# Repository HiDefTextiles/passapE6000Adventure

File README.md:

# Passap gögn
Kortlagning í formi dagbóka færslna af samasöfnuðum gögnum fræa veraldar vefnum.

Það eru tvennir hugar í þessum heimi:
* Croucher og Knitterstream.
	*	Hlaða inn .cut skrám með hámarkslengd og breidd
	*	Interface svo við consolið til að ná automation
* Bamberg og Irene.
	*	Fjarlægja consolið og tengja allt í arduino
	*	Lesa staðsetningu frá ljósa skynjurum
	*	Stýra nálum sjálf með innbygðu seglunum
Sjá dagbók hér að neðan.

# Passap E6000

# 2/5/24

Samskipti helgu við Chris ofthestreet og
Annacroucher
## TODO, Hvað er?
* WinCrea
* KnitterStream
* DIN port
* Hvaða útgáfu erum við með?

<!-- `Creating our own circuit board, since arduino is too bulky and attaching that into the console` -->

### DIN port
Í tölvupóstasamskiptum er mynd þar sem sýnt er 6 pin DIN port.

### WinCrea
forrit til að gera hannanir fyrir Passap e6000 outputar .cut fileum sem er síðan hægt að h
### KnitterStream
* Notast við arduino til að interface við takka á stýringu.
* Hleður inn skrám eins og hægt er í chipset 23+ 

### Hvaða útgáfu erum við með?

Croucher vill að maður viti hvaða chipset vélin hefur en lýsingar til að komast að því eru óskýrar og krefjast jafnvel þess að rífa hana í sundur sem ég hef ekki leyfi fyrir enn.

## Chipset test
[Diana Natters umfjöllun um passap e6000](https://diananatters.blogspot.com/2010/10/passap-e6000-battery-chipset.html)

If it says MEMO, then start at step 1.

Þegar vélin er ræst kemur upp MEMO

Vélin öskrar og við fáum error 213.

Hún getur því ekki tekið við niðurhöluðum skrám.

## Croucher

Við erum með id 7041398 > 7037001.
Skv skjölum frá croucher eigum við því að vera með download og 32kb minni. En testið sem ég gerði frá diönu gaf error 213. Las yfir documentation fræa croucher aftur og hann seigir að error 213 sé rétt. Rámaði í það að ég hefði séð þessa tölu áður. Diana skrifar óskýrt en þetta er þá komið núna. Við erum með stuðning við að downloada patternum.

Það eru til mismunandi týpur af vélinni.
Það var bætt við download support frá MSDOS og auka minni í nýrri vélunum.
Það er hægt að uppfæra í það og kaupa frá honum íhluti til þess. Hann mæli eindregi með því að maður leggji ekki í það að uppfæra minnið og virðast ekki vera miklir kostir til þess.

Hægt er að hlaða niður skjölum, .cut sem innihalda
leiðbeiningar um lita munstur upp að 4 litum.
0,1,2,3
Leiðbeiningar um uppsetningar slíkar skrár eru í skjölum sem croucher sendi.

Það skjal inniheldur header með 10 stöfum og svo munstrið.

* Litafjölda stafur [0,3,4]: HEX[30,33,34] = [1-2,3,4] Litir
* Bil: HEX[20]
* Breidd munsturs/dálkar á bilinu [bil,bil,1] til [1,8,0]
* Bil
* Lengd munsturs/raðir á bilinu [bil,bil,1] til [2,5,5]
* Bil
* Litamunstur þar sem hver tala merkir lit 0-3

Hef það á tilfinningunni að við séum með eldri týpu annars væri ég ekki að lesa tölvupósta frá 2014.

## Irene
[Irene](https://hackaday.io/project/163701-passap-e6000-rebuilt-and-replaced-console/details)
[Irene repo](https://github.com/IrenePassap/Passap-E6000-hacked-and-rebuilt/blob/master/Passap_Projekt_Raspberry_Pi_Version_36.3_23.7.21.py)

Hún notar eina raspberry pi sem stýrir svo þrem arduino vélum. ein fyrir motor til að færa fram og til baka, ein fyrir fremri 'lock' til að prjóna og aðra fyrir aftari 'lock'.

Hún er búin að breyta vélinni þannig að aftara borðið er eins og fremra og getur þá líka prjónað eh meira fancy.

Hún vitnar í [bamberg](https://www.hackerspace-bamberg.de/Passap_pfaff_e6000)
.

Bamberg talar 'lightbarriers' í "carriage" til að vita staðsetninguna.

Finnst líklegt að við þurfum bara einfaldlega að losta okkur við upprunalgeu stýringuna eins og aðrir hafa gert. Þá kemur upp vandamál Croucher um að þú þarft í raun að forrita allt frá grunni með mikilli vitneskju um prjón og vélbúnaðinn.

## Niðurstöður // Summary

Erum með stuðning við að downloada .cut fileum.

Höfum 32k chip en 20k minni skv nýtni áætlun croucher.

Irene og bamberg hafa fjarlægt consolið gjörsamlega og smíðað sitt eigið með raspberry pi.

Ég held að við viljum halda consolinu og allri tækninni þar inni. grf.

Spurning um að bæta þá ofaná eh stýringu sem interfacer við consolið. Skoða knitterstream betur.

# 3/5/24

Byrjum á að skoða Irene og Bamberg betur.

* [Bamberg Github](https://github.com/knitty/firmware/tree/master/software/Knitty)
* [Bamberg lýsing (þýsk)](https://www.hackerspace-bamberg.de/Passap_pfaff_e6000)
* [Irene Github](https://github.com/IrenePassap/Passap-E6000-hacked-and-rebuilt)
* [Irene dagbók](https://hackaday.io/project/163701-passap-e6000-rebuilt-and-replaced-console/details)

## Diagram
### Bamberg

Arduino unoinn kemur í stað stýringarinar 'consolsins' og notast þeir við sitt eigið forrit sem þeir gerðu fyrir alíka vél sem heitir [knitty](https://www.hackerspace-bamberg.de/Knitty)

Þeir eru líka með sér arduino fyror Autocolor, hvort hann hafi verið eh bilaður hjá þeim. Sé þetta ekki hjá Irene

[`Hægt er að sjá .svg diagram myndir frá Bamberg`](https://github.com/knitty/firmware/tree/master/hardware)

### Irene

Irene byggir á Bamberg en í stað þess að vera með tölvu usb tengda í arduino uno þá er raspberry pi með notendaviðmót sem stýrir

Lesa kóðan þeirra og skilja hvernig þau eru að lesa inn staðsetningu með pinum frá ljósunum. Þetta virðist ekki flókið en erfitt að ná hausnum almennilega utanum þetta án  þess að fikta sjálfur.

<a href="https://hackaday.io/project/163701-passap-e6000-rebuilt-and-replaced-console/details" style="text-align:center;">Sjá meira hjá Irene</a>
Light sensorinn skýnir ljósi í 2mm göt á guiderail, 3mm á milli gata, 5mm er ein nál.

út frá munstri er hægt að lesa staðsetningu og átt lásins.

Ég bætti við Repoinu hennar Irene og bamber hér í möppu, til að auðvelda mér að fina efnið og rýna í það.

# 6/5/24

## Irene
Raspberry with two arduino sem stýra sitthvorum lásnum.
Hann stýrir svo mótornum. Það er ekkert samband á milli mótors og lása.

Mótorinn ýtir lásonum fram og til baka eins og ef noandi væri að gera það með hendinni og
lásarnir eru með ljós skynjara sem þeir nota til að lesa átt og staðsetningu.

Irene notast við technique.txt skrár fyrir gerð af prjóni?
Sva aðra skrá fyrir pattern.

Kóðarnir hennar eru torlesnir og gætu verið mun betur skrifaðir. Allar breytur eru global. Numpy er ekki notað fyrir fylki heldur forlykkju viðbjóður.

Ég tek það á mig að fara í gegnum þetta línu fyrir línu og endurskrifa allavega python kóðan uppá skilning fyrir mig. Besta leiðin til að skilja eitthvað er að laga það.

Þetta endar alltaf á því að maður þarf að fikta og prufa sig áfram.

Ég er búin að minnka fyrstu 800 línurnar niðu í minna en 200 með einfaldri notkun á numpy og skilning a fylkja notkun. Hægt er að sjá hreinskrifuðu útgáfuna undir möppunni Irene með nafninu controler-elli-cleanup.py

ég held áfram með þetta á morgun eftir hreinsun á vél

# 7/5/24

Þrif og teambonding

# 8/5/24

Punktar um gpio merki.

Til að fá gpio input í program er hægt að framkvæma "polling".
Getur misst af inputi ef gidli er lesið á vitlausum tíma.
Gert í lykkjum og er mögulega íþungt á keyrslu umhvefið.
Öunnr aðferðir er að nota "interrupts" sem tekur eftir muninum á milli breytingum, frá hi to low (falling) frá low to hi (rising)

Kláruðum að þrífa.

Skoðaði betur munninn á tölvu og mekanísku útgáfunni frá Passap.

Tölvu útgáfan er með 
- 2 input, ljósskynjararnit tveir sem staðsetjan
- 2 output, seglar sem raða nálum fyrir munstur næstu línu
Sameiginlegt er
- Mekaníkinn sem ýtir nálonum upp er sú sama.
- nálabeðið er óbreytt

# 10/5/24

Öll ljós slökkt og ekki sál að sjá.

Er komin með 250 línur af hreinskrifaðari kóða útgáfu frá Irene.

Er að bryja á tech array hjá henni.

Hér útskýrist betur þessi blessaði tech array file hjá henni.

fyrstu tvö gildin lýsir hún sem skipun um að byrja pattern á nýrri línu.

```
    x = tech_Array[countTech][0]
    x = int(x)
    rowCount_VNB = int(rowCount_VNB) + x
```

Þar sem rowcount_VNB er nr línu á fremri lásnum.
countTech er lína í tech file, 0 er index á fyrstu tölunni

Næst koma hvaða lita vigra hún nota.
Þar er gefin strengur sem er enumaður á skipun sem sendir viðeigandi vigur á viðeigandi Arduino.

V - fremri, H - Aftari

Svo er stillingin sem að lásin á að vera í. Hún stilir það sjálf

svo skipanir til að skipta um lit, sem ég skil ekki alveg.

Hún seigir að þetta sé boolean já og nei fyrir skipti og stop en þegar hún skiptir um lit breytast þesssi gildi ekki neitt.

svo bara info dump, þetta væri vel hægt að sleppa.

Virkni segla lásins voru í raun sanreynd í prufunum í dag. 
Hann stillit uppröðunninni fyrir næstu umferð. Default er 1 þarf að senda 0 til að setja í hvildarstöðu.
Pusherarnir stýra svo einhvernveginn hvaða nálar eru notaðar.
Það er bara hlustað á pusherana þegar x stilling er virk og þegar kveikr er á örvum í gömlutýpunni er uppröðun þeirra breytt.

Þetta væri þá hægt að þýða yfir í kóða og sleppa motor stýringum.

Prufurnar gengu þó eh og gott að sjá mekaníkinn í virkni.

# 15/5/24

## Prototype 1

Staðan í dag, komin með arduino tengingu við lásinn. Get lesið ljósskynjara og breytt segulsviði seglana.

Þá er bara að stúttera bamberg og irene stýringarnar.

Næ að láta intterupt virka fyrir PIN_CSENSE en ekki PIN_CREF, en hann skynjar breytt gildi á báðum þannig við látum eina innterrupt rútínu virka

Fyrir Vinstri til hægri koma gildin

40 & 31

Fyrir hægri til vinstri fáum við gildin

41 & 30

Úr innterrupt rútinum hennar Irene

# 16/5/24

## Prototype 2
Ný rás fræsuð, viðnám lóðuð, tengi og pinnar.

Skynjarar í lagi, skipti út powersupply fyrir annað sem ég fann liggjandi í vr 3 og seglarnir virka.

Þá er bara eftir að útfæra kóða sem samnýtir hreyfingu

# 17/5/24

CREF er ekki tengt í pinna sem styður interrupt.

Vélin stíflaðist, tók hana í sundur, sem er fínt. Hafði langað að gera það til að sjá pusherana betur.

# 21/5/24

Horfði upp undir pusherana til að sjá hvar þeir byrja að raðast eftir stillingu. Breytti svo stillingunni og sá hversu margir pusherar voru á milli þess að breytinginn skilaði sér. Merkti þann punkt á velina og notaði hann sem calibration punkt.

Þetta er punkturinn þar sem röðun pusherana er ákveðin. Hvort þeir fara upp eða niður. Miðaði svo við þann punkt og prófaði að færa hann eitt nálarbeð í einu og breyta stillingu til að sannreyna og það gekk. 

Notaði svo ljósaskynjarann og las hvaða munstur kom úr interruptinu í hvert skipti sem ég færði calibration/samstillingar punktinn á milli nálarbeða. 

Tölugildin eru því 41 og 31 eða 11 og 01;
11: Cref=1 & Csense=1;
01: Cref=0 & Csense=1;

Til að staðsetja lásin á nálarbeðinu tökum við hann alveg út í enda. Rennum honum svo hægt inná leiðarvísirinn og greinum gildi.

Út frá því fáum við alla punkta. Það ætti að vera nóg að gera þetta bara í eina átt. Frá vinstri til hægri, horft beint á fremri lásin. Því Hægri til vinstri ætti í raun bara að telja niður sömu gildi, allavega fyrir nálarbeðin, jaðar punktarnir gætu verið annað mál. SKoðum það þegar þar að kemur

Punktar fyrir kvörðun á nálabeða ás útfrá ljósskynjara

Upphafsgildi breyturnar state & counter eru 0;
```
// direction
volatile int state = 0;
// position
volatile int counter = 0;
```

State seigir okkur um stöðu beggja ljósskynjarana og útfrá því getum við ákvarðað átt. Counter telur hverja nál og er ætlað til að staðsetja okkur.

Með state ákvöðrum við hvort við hækkum eða lækkum counter, út frá counter fáum við staðetningu

# 22/5/24

Villur lagaðar og ás nálabeðs kvarðaður.

Til að kvarða nálabeðið þarf að taka lásinn/sleðann af. Endurkveikja á arduino og renna honum á.

// 30 0
// 31 0

// 31 0
// 40 -1
// 41 0
// 40 -1
// 41 0
// 40 -1

// byrjar 31 0
// svo mynztur 40 - 41
// byrjar loks 41 - 30
// í 28 erum við komin á fyrstu nálina
// 207 seinasta nál || 206
// 243 auto color endir
// 221 útaf hægri

# 23/5/24

Munztrið sem kemur þegar honum er rennt á er, 40 telur niður og 41 upp

31 - 0
40 - -1
41 - 0
40 - -1
41 - 0
40 - -1
41 - 0 // 41-30 nála munustur++
30 - 0
41 - 1

28 er nál 1 og 206 nál 179

## Kenning 

Nálabeðið er samhverft og merkt með heiltölum í báðar áttir frá miðju með 

90 nálar vinstra megin

89 nálar hægra megin

Tölvur byrja í núlli, þannig ef fyrsta nálinn vinstra megin við miðju er 0
þá er nálabeðið samhverft um hana í hugbúnaðinum það er

-89 0 89.

## Framkvæmd

Við viljum að notandinn geti skilgreint fyrstu nál til vinstri. Best væri að notandinn gæti notast við innbygpu tölurnar á vélinni.

Notandi segir að munztur byrji á nál 90 til vinstri, þá þarf það að vera 0 í munztur vigri.

setur inn -90,
sem er nál 28
### Hugmynd
```
int input = -90;
int start = (input < 0) ? input +90 : input + 89;
int line = 0;
counter - 28 - (start) = 0;
206 - 28 = 179
if (counter >= (28+start) && counter < 207)
{
	int index = counter - 28 - start;
	digitalWrite(pin,PatternMatrix[index])
	if (counter > width of matrix + start || (line>0 && counter < 28+start))
	{
		line++
	}
}

counter - 28 + input = 0
```

### útfærsla
Notobene þetta eru 178 nálar og við byrjum í 0,
þannig index er á bilinu 0-177, fyrir allar nálar á borðinu

#### Einn vídd Index
```
    int input = -90;
    int start = (input < 0) ? input + 90 : input + 89;
    int index = counter - 28 - start;
```
If var óþarfi þar sem við setjum bara núll punkt og okkur ætti að vera sama um öll önnur gildi. Þannig þótt index flæði út fyrir þá er hann ekki að stýra neinu.

Þegar ég var að prufukeyra index, var ljost að þar sem seglarnir eru ekki á samastað þá þarf að vera með sér tölu fyrir hvorn, það virðist vera 10 nála bil á milli, þannig við bara bætum við 10 á bakaleiðinni við index. einnig virtist vera 2 nála offset frá fyrstu nál og stillingar punkti, sem er innan skekkju marka mannsins.

vona ég.

ég breytti því núll punkti nálarásins í 26 til að lagfæra það.

```
		int input = -10;
		int start = (input < 0) ? input + 90 : input + 89;
		int index = counter - 26 - start;
		int value = 1;
```
##### Hægri til vinstri
```
			if (index + 10 >= 0 && index + 10 < arraysize)
			{
				value = array[index + 10];
			}
			digitalWrite(PIN_NEEDLE_RTL, value);
```
##### Vinstri til hægri
```
			if (index >= 0 && index < arraysize)
			{
				value = array[index];
			}
			digitalWrite(PIN_NEEDLE_LTR, value);

```
#### Tveggja vídda Index
Þá er það línu meðhöndlun.

Byrjum alltaf að prjóna hægri til vinstri.
Setjum alltaf lásinn/sleðann á frá vinstri til hægri.

Þurfum þá að stilla nálarnar þannig fyrst.

Þannig sleðin byrjar alltaf lengst til vinstri?
vonandi

# 27/5/24

Fann kennslumyndbönd á netinu um það hvernig maður sendir skipanir frá python yfir á arduino.

## Næstu ítranir // TODO
- Útfæra grunn að samskiptum á milli arduino og umheimsins
	- Bæta við raspberry pi
	- bakenda
	- python/javascript?
- Bæta við motor // skoða
	- mögulega motor stýringu
	- Hægt að vita staðsetningu autocolor

# 28/5/24

Takmarkanir á gögnum send til arduino.

Ef við notum streng þá getur hann verip með 768 stafi.

Ef við sendjum

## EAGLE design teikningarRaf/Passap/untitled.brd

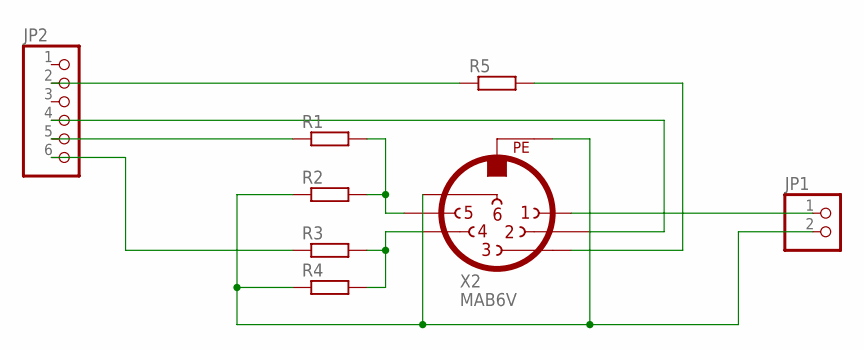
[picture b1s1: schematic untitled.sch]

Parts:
JP1: PINHD-1X2; 1X02
JP2: PINHD-1X6; 1X06
R1, R2, R3, R4: R-EU_0204/7; 0204/7
R5: R-EU_0207/15; 0207/15
X2: MAB6V

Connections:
GND: JP1.2, R2.1, R4.1, X2.6, X2.PE
unnamed: R1.2, R2.2, X2.5
unnamed: R3.2, R4.2, X2.4
unnamed: R5.2, X2.3
unnamed: JP2.5, R1.1
unnamed: JP2.6, R3.1
unnamed: JP2.4, X2.2
unnamed: JP2.2, R5.1
unnamed: JP1.1, X2.1

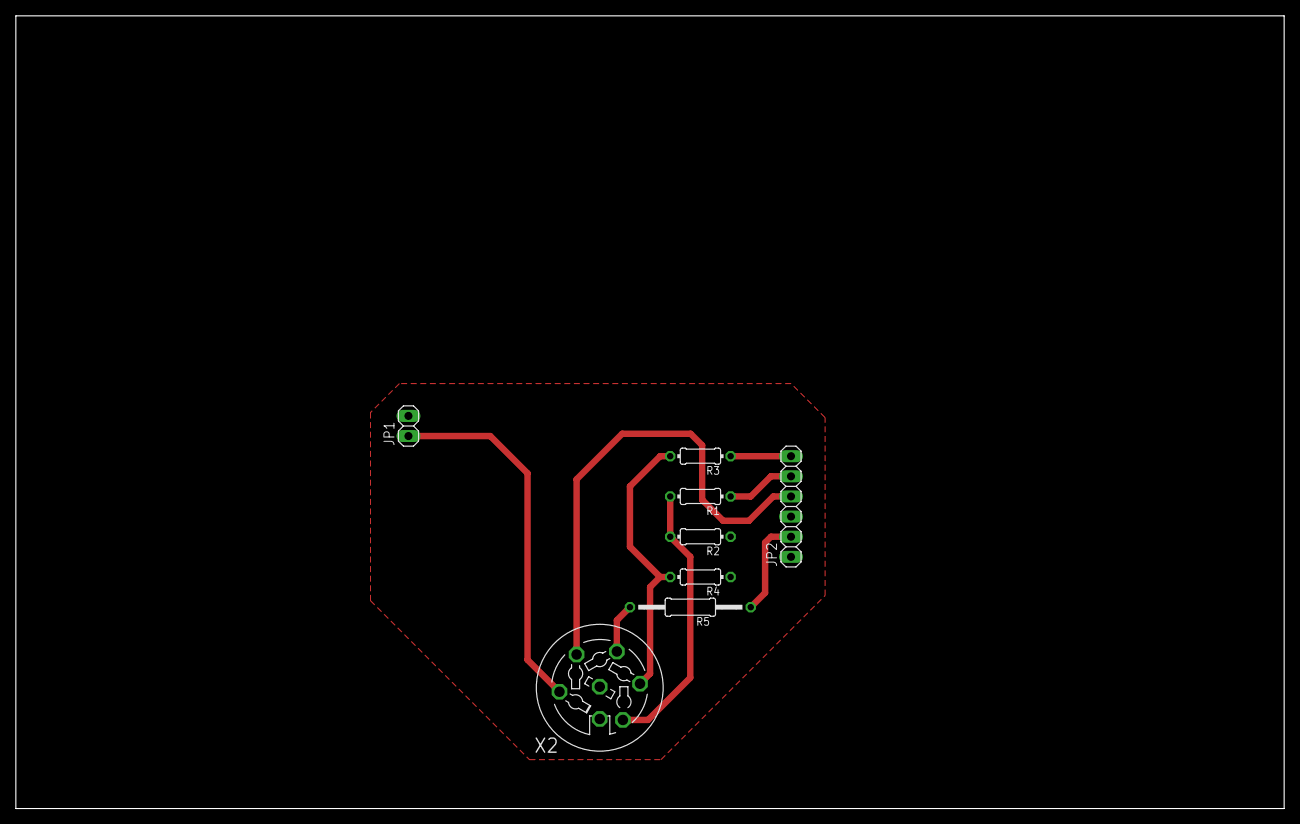
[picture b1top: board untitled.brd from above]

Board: 2 copper layers, 160.0 x 100.0 mm, 8 parts (0 on the bottom side), 9 nets.

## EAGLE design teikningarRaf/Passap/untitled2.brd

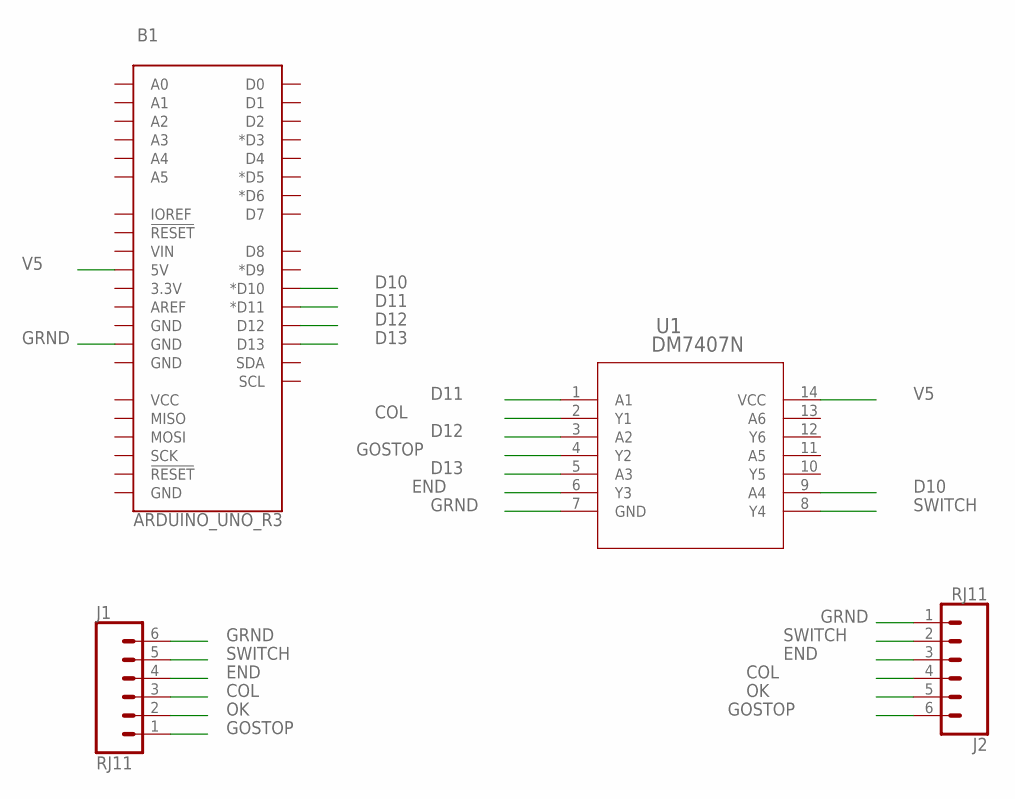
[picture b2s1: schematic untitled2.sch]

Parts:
B1: ARDUINO_UNO_R3; ARDUINO_R3
J1, J2: RJ11; RJ11-6
U1: DM7407N; PDIP14_6P35X19P56_ONS

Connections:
COL: J1.3, J2.4, U1.2 (Y1)
D10: B1.D10 (*D10), U1.9 (A4)
D11: B1.D11 (*D11), U1.1 (A1)
D12: B1.D12, U1.3 (A2)
D13: B1.D13, U1.5 (A3)
END: J1.4, J2.3, U1.6 (Y3)
GOSTOP: J1.1, J2.6, U1.4 (Y2)
GRND: B1.GND@3 (GND), J1.6, J2.1, U1.7 (GND)
OK: J1.2, J2.5
SWITCH: J1.5, J2.2, U1.8 (Y4)
V5: B1.5V, U1.14 (VCC)

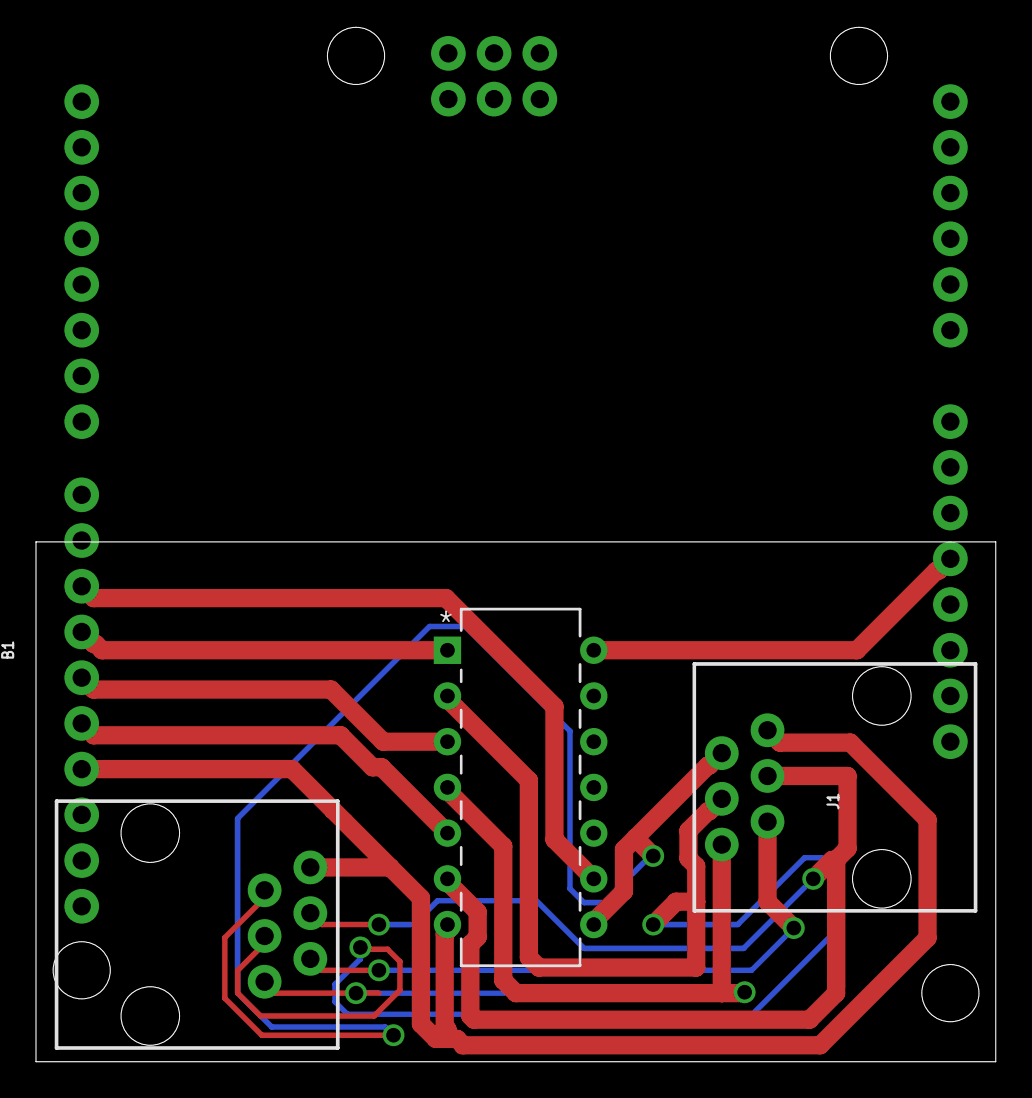
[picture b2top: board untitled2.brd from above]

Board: 2 copper layers, 53.3 x 28.9 mm, 4 parts (0 on the bottom side), 11 nets.

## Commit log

2024-05-03 test
2024-05-03 skrifaði stutt readme
2024-05-03 Lesefni
2024-05-06 Hef þetta repo bara fyrir gagnasöfnun og dagbók
2024-05-10 5/10 seglafatting
2024-05-24 vigur stuðningur og enda skilgrening hardcode
2024-05-29 Serial munztur stillingar komnar
2024-07-14 pyhon pattern send to server
2024-09-23 teikningar

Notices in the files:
parts and their libraries:
SparkFun-Boards: Licensing: Creative Commons ShareAlike 4.0 International - https://creativecommons.org/licenses/by-sa/4.0
COPYRIGHT: Copyright (C) 2024 Ultra Librarian. All rights reserved.
